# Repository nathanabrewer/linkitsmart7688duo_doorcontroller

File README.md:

# linkitsmart7688duo_doorcontroller

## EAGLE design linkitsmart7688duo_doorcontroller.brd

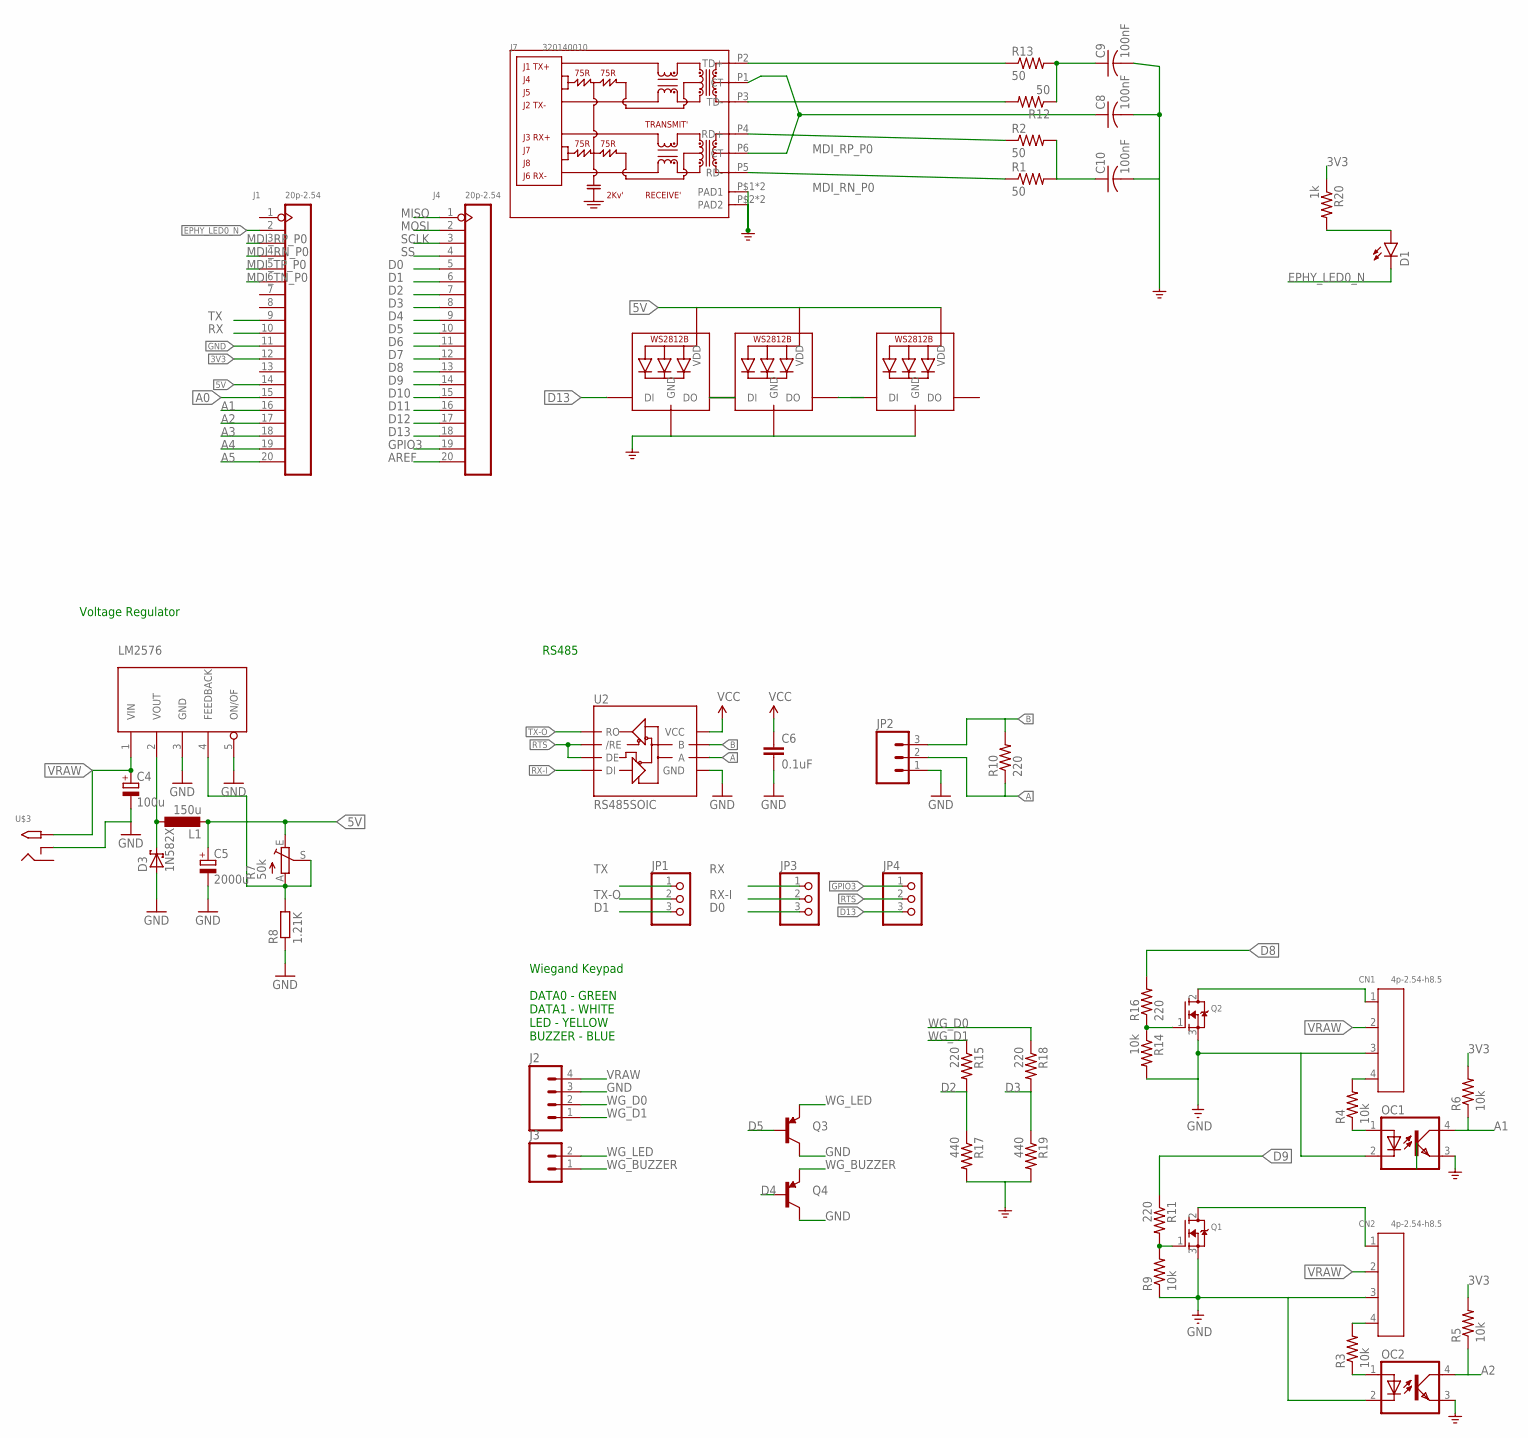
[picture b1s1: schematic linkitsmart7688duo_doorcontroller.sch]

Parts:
C4: 100u; E3,5-10; MPN UPW1E101MED
C5: 2000u; E7,5-18; MPN ERJ-14NF2000U
C6: 0.1uF; 0603-CAP; MPN 104M06QC100
C8, C9, C10: 100nF; C025-024X044
CN1, CN2: 4p-2.54-h8.5; H4-2.54-8.52X6.3MM
D1: LED3MM
D3: 1N582X; DO201T15
J1, J4: 20p-2.54; H20-2.54
J2: M04SCREW; SCREWTERMINAL-3.5MM-4
J3: M023.5MM; SCREWTERMINAL-3.5MM-2
J7: 320140010; RJ45-MJ6-BX11-RVS1T073
JP1, JP3, JP4: PINHD-1X3; 1X03
JP2: M03SCREW; SCREWTERMINAL-3.5MM-3
L1: 150u; MY-INDUCTANCE; MPN ACS770KCB-150U-PFF-T
LED4, LED5, LED6: WS2812B_5050N; WS2812B-NARROW
OC1, OC2: PC817; DIL04
Q1, Q2: MOSFET-NGDS_TO220V; TO220V; MPN SM6T68A
Q3, Q4: TRANSISTOR_PNPBC558; TO-92-AMMO
R1, R2, R12, R13: 50; 0805-THM
R3, R4, R5, R6, R9, R14: 10k; 0805-THM
R7: 50k; RJ9W; MPN MC00625W04021150K
R8: 1.21K; 0204/7; MPN ERJ-8ENF1211V
R10: 220; 0603-RES; MPN C0603C221K5RACTU
R11, R15, R16, R18: 220; 0805-THM
R17, R19: 440; 0805-THM
R20: 1k; 0805-THM
U2: RS485SOIC; SO08; MPN ADM4850ARZ
U$1: LM2576; TO220-5; MPN LM2576T-12/NOPB
U$3: 2.1MMJACKTHM; PJ-102A

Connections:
3V3: J1.12, R5.2, R6.2, R20.1
5V: C5.+, C6.1, J1.14, L1.P$2 (2), LED4.1-VDD (VDD), LED5.1-VDD (VDD), LED6.1-VDD (VDD), R7.E, U2.8 (VCC)
A: JP2.2, R10.1, U2.6 (A)
A0: J1.15
A1: J1.16, OC1.4 (COL), R6.1
A2: J1.17, OC2.4 (COL), R5.1
A3: J1.18
A4: J1.19
A5: J1.20
AREF: J4.20
B: JP2.3, R10.2, U2.7 (B)
D0: J4.5, JP3.3
D1: J4.6, JP1.3
D2: J4.7, R15.2, R17.1
D3: J4.8, R18.2, R19.1
D4: J4.9, Q4.2 (B)
D5: J4.10, Q3.2 (B)
D6: J4.11
D7: J4.12
D8: J4.13, R16.2
D9: J4.14, R11.1
D10: J4.15
D11: J4.16
D12: J4.17
D13: J4.18, JP4.3, LED4.4-DIN (DI)
EPHY_LED0_N: D1.K (C), J1.2
GND: C4.-, C5.-, C6.2, C8.2, C9.2, C10.2, CN1.3, CN2.3, D3.A, J1.11, J2.3, J7.P$1 (PAD1), J7.P$2 (PAD2), J7.PAD1, J7.PAD2, JP2.1, LED4.3-GND (GND), LED5.3-GND (GND), LED6.3-GND (GND), OC1.2 (C), OC1.3 (EMIT), OC2.2 (C), OC2.3 (EMIT), Q1.3 (S), Q2.3 (S), Q3.1 (C), Q4.1 (C), R8.1, R9.1, R14.2, R17.2, R19.2, U2.5 (GND), U$1.3 (GND), U$1.5 (ON/OF), U$3.RING_SW
GPIO3: J4.19, JP4.1
MDI_RN_P0: J1.4, J7.P5 (RD-), R1.1
MDI_RP_P0: J1.3, J7.P4 (RD+), R2.1
MDI_TN_P0: J1.6, J7.P3 (TD-), R12.2
MDI_TP_P0: J1.5, J7.P2 (TD+), R13.1
MISO: J4.1
MOSI: J4.2
unnamed: R7.A, R7.S, R8.2, U$1.4 (FEEDBACK)
unnamed: D3.C, L1.P$1 (1), U$1.2 (VOUT)
unnamed: Q1.1 (G), R9.2, R11.2
unnamed: CN2.1, Q1.2 (D)
unnamed: C8.1, J7.P1 (CT), J7.P6 (CT)
unnamed: CN1.1, Q2.2 (D)
unnamed: Q2.1 (G), R14.1, R16.1
unnamed: C9.1, R12.1, R13.2
unnamed: CN1.4, R4.2
unnamed: C10.1, R1.2, R2.2
unnamed: OC2.1 (A), R3.1
unnamed: D1.A, R20.2
unnamed: LED4.2-DOUT (DO), LED5.4-DIN (DI)
unnamed: LED5.2-DOUT (DO), LED6.4-DIN (DI)
unnamed: CN2.4, R3.2
unnamed: OC1.1 (A), R4.1
RTS: JP4.2, U2.2 (/RE), U2.3 (DE)
RX: J1.10, JP3.1
RX-I: JP3.2, U2.4 (DI)
SCLK: J4.3
SS: J4.4
TX: J1.9, JP1.1
TX-O: JP1.2, U2.1 (RO)
VRAW: C4.+, CN1.2, CN2.2, J2.4, U$1.1 (VIN), U$3.TIP
WG_BUZZER: J3.1, Q4.3 (E)
WG_D0: J2.2, R18.1
WG_D1: J2.1, R15.1
WG_LED: J3.2, Q3.3 (E)

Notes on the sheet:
Voltage Regulator
RS485
Wiegand Keypad DATA0 - GREEN DATA1 - WHITE LED - YELLOW BUZZER - BLUE

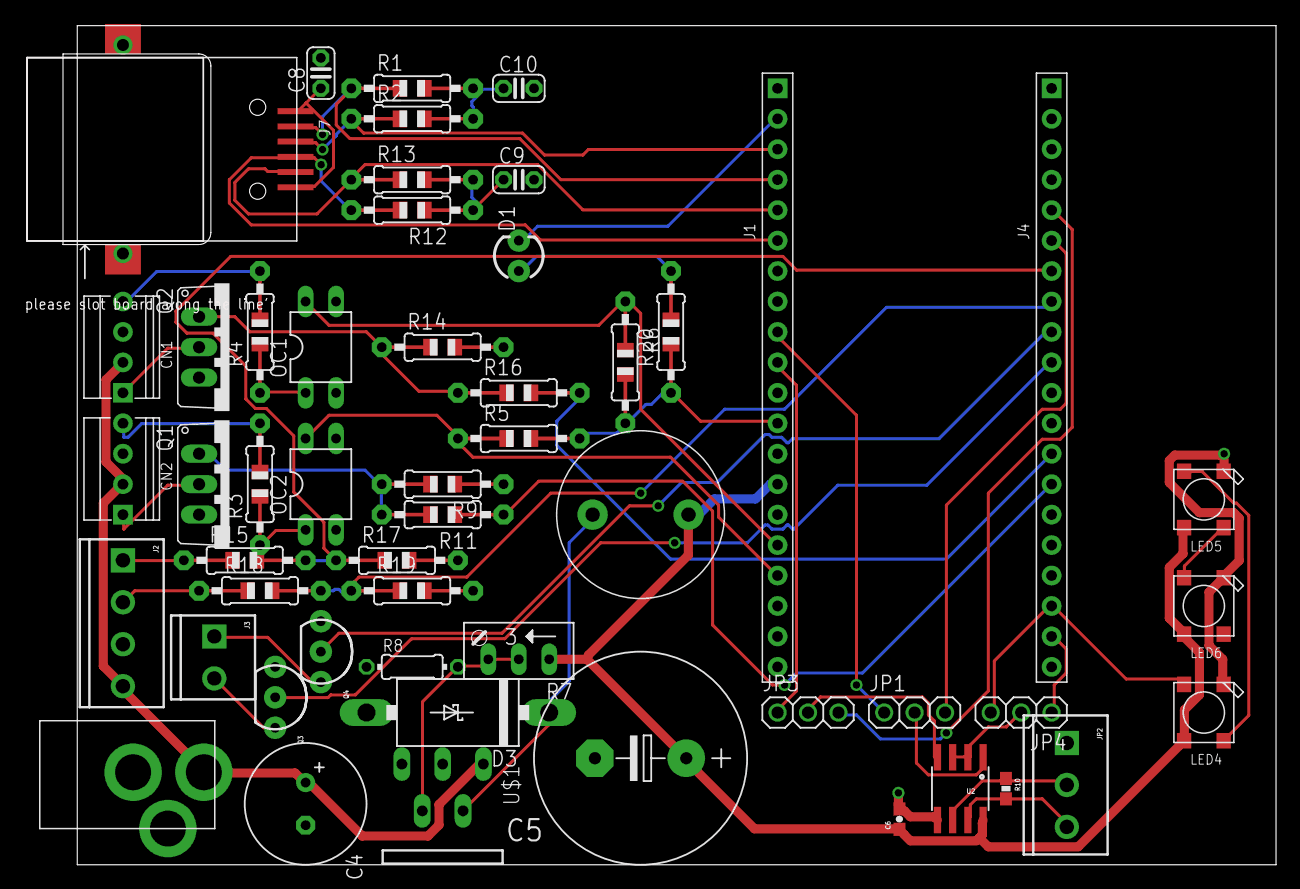
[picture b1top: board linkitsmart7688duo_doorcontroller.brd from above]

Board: 2 copper layers, 104.3 x 69.9 mm, 52 parts (0 on the bottom side), 48 nets.

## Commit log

2016-12-05 Board with RS485, Mosfets instead of relays, voltage divider and PNP transistors instead of 5v to 3v logic shifter on wiegand keypad interface
2016-12-05 labeled stuff in schematic

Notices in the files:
parts and their libraries:
SparkFun-Capacitors: Licensing: Creative Commons ShareAlike 4.0 International - https://creativecommons.org/licenses/by-sa/4.0
